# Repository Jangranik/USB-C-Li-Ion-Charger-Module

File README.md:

# USB-C-Li-Ion-Charger-Module

Specs
	
Input	USB-C, 5 V

Battery	1-cell Li-ion, 3.7 V nominal 

Charger	TI BQ24074 (linear charger with power-path management)

Boost	TI TPS61088 synchronous boost

Output 5.1 V regulated

Board	2-layer  

It outputs 4.1V with just the USB-C connected. The BQ24074 feeds the system rail and charges the battery at the same time, so the board would keep running from the USB while the battery charges and switches to the battery once the USB is unplugged. The system then feeds into the TPS61088 which steps it up to 5.1V output.

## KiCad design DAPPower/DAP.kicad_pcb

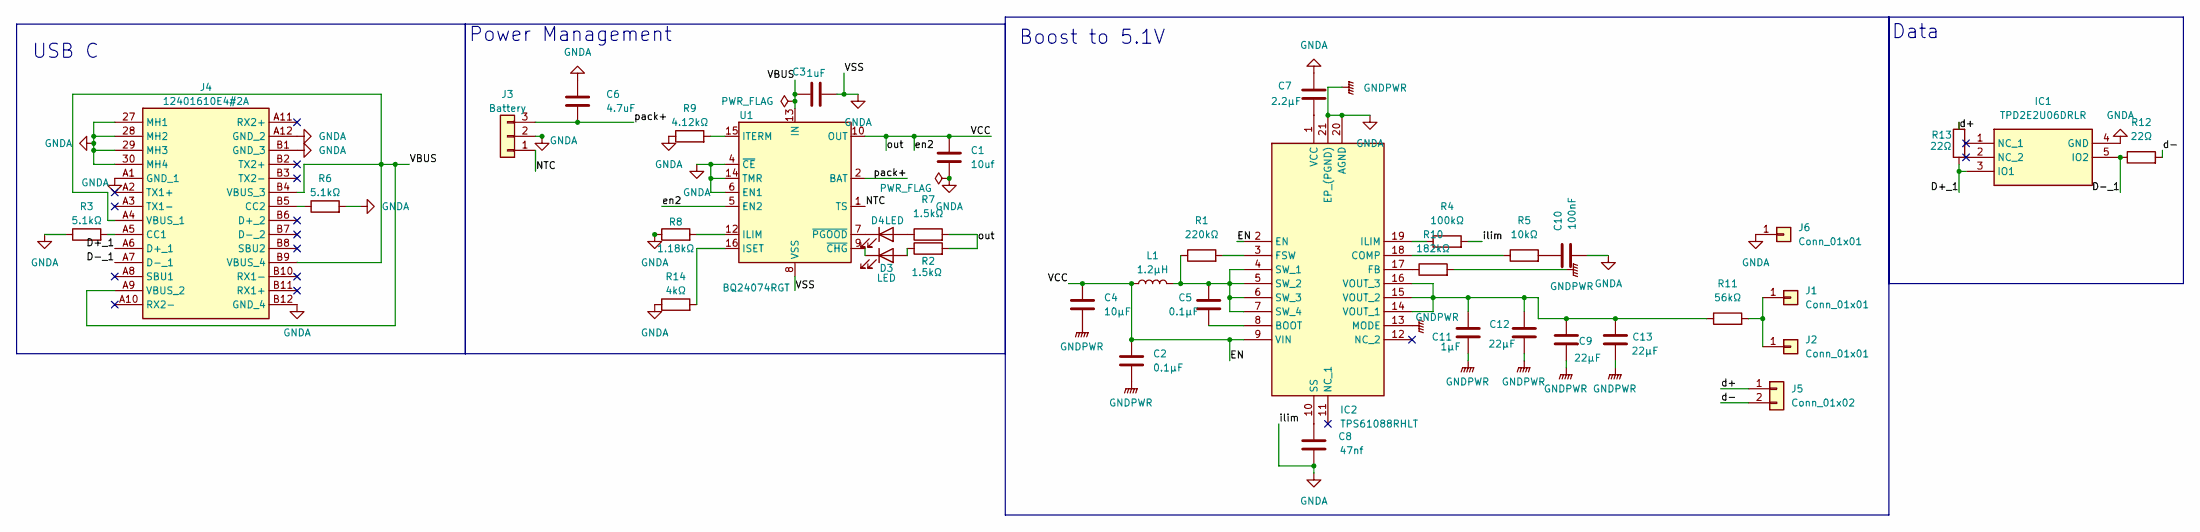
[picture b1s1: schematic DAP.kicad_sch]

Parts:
C1: 10uf; C_0805_2012Metric
C2, C5: 0.1µF; C_0402_1005Metric
C3: 1uF; C_0201_0603Metric
C4: 10µF; C_0805_2012Metric
C6: 4.7uF; C_0805_2012Metric
C7: 2.2µF; C_0402_1005Metric
C8: 47nf; C_0402_1005Metric
C9, C12, C13: 22µF; C_1206_3216Metric
C10: 100nF; C_0402_1005Metric
C11: 1µF; C_0805_2012Metric
D3, D4: LED; LED_0805_2012Metric
IC1: TPD2E2U06DRLR; Mouser Part Number 595-TPD2E2U06DRLR
IC2: TPS61088RHLT; Mouser Part Number 595-TPS61088RHLT
J1, J2, J6: Conn_01x01; SolderWire-0.5sqmm_1x01_D0.9mm_OD2.1mm
J3: Battery; JST_PH_S3B-PH-K_1x03_P2.00mm_Horizontal
J4: 12401610E4#2A; Manufacturer_Part_Number 12401610E4#2A
J5: Conn_01x02; SolderWire-0.5sqmm_1x02_P4.6mm_D0.9mm_OD2.1mm
L1: 1.2µH; L_Sumida_CDMC6D28_7.25x6.5mm
R1: 220kΩ; R_0402_1005Metric
R2, R7: 1.5kΩ; R_0402_1005Metric
R3, R6: 5.1kΩ; R_0402_1005Metric
R4: 100kΩ; R_0402_1005Metric
R5: 10kΩ; R_0402_1005Metric
R8: 1.18kΩ; R_0402_1005Metric
R9: 4.12kΩ; R_0402_1005Metric
R10: 182kΩ; R_0402_1005Metric
R11: 56kΩ; R_0402_1005Metric
R12, R13: 22Ω; R_0402_1005Metric
R14: 4kΩ; R_0402_1005Metric
U1: BQ24074RGT; VQFN-16-1EP_3x3mm_P0.5mm_EP1.6x1.6mm

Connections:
/D+_1: IC1.3 (IO1), J4.A6 (D+_1), R13.1
/D-_1: IC1.5 (IO2), J4.A7 (D-_1), R12.1
/EN: C1.1, C2.1, C4.1, IC2.2 (EN), IC2.9 (VIN), L1.1, R2.2, R7.2, U1.5 (EN2), U1.10 (OUT), U1.11 (OUT)
/NTC: J3.1, U1.1 (TS)
/VBUS: C3.1, J4.A4 (VBUS_1), J4.A9 (VBUS_2), J4.B4 (VBUS_3), J4.B9 (VBUS_4), U1.13 (IN)
/d+: J5.1, R13.2
/d-: J5.2, R12.2
/pack+: C6.2, J3.3, U1.2 (BAT), U1.3 (BAT)
unnamed: C10.1, R5.2
unnamed: D3.2 (A), R2.1
unnamed: D3.1 (K), U1.9 (~CHG)
unnamed: D4.2 (A), R7.1
unnamed: D4.1 (K), U1.7 (~PGOOD)
unnamed: C5.2, IC2.8 (BOOT)
unnamed: IC2.18 (COMP), R5.1
unnamed: IC2.17 (FB), R10.1
unnamed: IC2.3 (FSW), R1.2
unnamed: IC2.19 (ILIM), R4.1
unnamed: C8.1, IC2.10 (SS)
unnamed: C5.1, IC2.4 (SW_1), IC2.5 (SW_2), IC2.6 (SW_3), IC2.7 (SW_4), L1.2, R1.1
unnamed: C7.2, IC2.1 (VCC)
unnamed: C9.2, C11.2, C12.2, C13.2, IC2.14 (VOUT_1), IC2.15 (VOUT_2), IC2.16 (VOUT_3), R11.1
unnamed: J1.1, J2.1, R11.2
unnamed: J4.A5 (CC1), R3.2
unnamed: J4.B5 (CC2), R6.1
unnamed: R8.2, U1.12 (ILIM)
unnamed: R14.2, U1.16 (ISET)
unnamed: R9.2, U1.15 (ITERM)

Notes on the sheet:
USB C
Data
Boost to 5.1V
Power Management

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
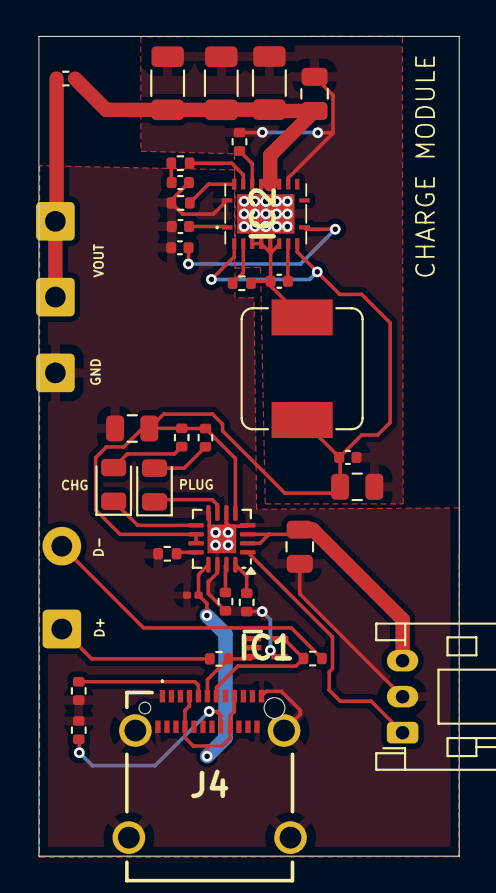
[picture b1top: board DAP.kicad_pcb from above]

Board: 2 copper layers, 23.4 x 45.5 mm, 39 parts (0 on the bottom side), 30 nets.
